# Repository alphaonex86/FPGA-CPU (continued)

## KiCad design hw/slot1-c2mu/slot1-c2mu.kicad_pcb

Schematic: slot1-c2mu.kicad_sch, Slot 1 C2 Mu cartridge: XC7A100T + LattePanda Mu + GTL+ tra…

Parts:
C1: 100uF/25V; CP_Elec_6.3x5.4
C2, C3, C10, C14, C18: 10uF/25V; C_1210_3225Metric
C4: 4.7uF/25V; C_0805_2012Metric
C5, C6: 22uF/10V; C_1206_3216Metric
C7, C12, C16, C20, C93, C94, C95, C96, C97, C98, C99, C100, C101, C102, C103, C104, C105, C106, C107, C108, C109, C110, C111, C112, C113, C114, C115, C116, C117, C118, C119, C120, C121, C122, C123, C124, C133, C134, C135, C136, C137, C138, C139, C141, C142, C146, C147, C148, C149, C150, C151, C169, C170, C171: 100nF; C_0402_1005Metric
C8: 10nF; C_0402_1005Metric
C9: 27nF; C_0402_1005Metric
C11, C15, C19: 22uF/6.3V; C_0805_2012Metric
C13, C17, C21: 3.3nF; C_0402_1005Metric
C22, C23, C24, C25, C26, C27, C28, C29, C30, C31, C32, C33, C34, C35, C36, C37, C38, C41, C42, C43, C44, C45: 470nF; C_0402_P1.00
C39, C40, C46, C47, C48, C49, C50, C51, C52: 470nF; C_0402_1005Metric
C53, C54, C55, C56, C57, C58, C59, C60, C61, C62, C63: 100nF; C_0402_P1.00
C64, C65: 100uF/6.3V; C_1210_3225Metric
C66, C67, C68, C69, C70, C71, C74, C75, C76, C77, C78, C83, C84, C85, C86, C87, C88, C89, C90, C91, C92, C140, C143: 4.7uF; C_0603_1608Metric
C72, C73, C79, C80, C81, C82: 47uF/6.3V; C_1210_3225Metric
C125, C126, C129, C130: 1uF; C_0402_1005Metric
C127, C131: 2.2uF; C_0402_1005Metric
C128, C132: 1nF; C_0402_1005Metric
C144, C145: 22uF; C_0805_2012Metric
C152: 10pF; C_0402_1005Metric
C153, C154, C155, C156, C157, C158, C159, C160, C161, C162, C163, C164, C165, C166, C167, C168: 220nF; C_0402_1005Metric
C172: 10uF; C_0805_2012Metric
C173, C174: 27pF; C_0402_1005Metric
D1: green; LED_0603_1608Metric
D2: B5819WS; D_SOD-323
F1: 5A; Fuse_1812_4532Metric
F2: 1.1A; Fuse_1206_3216Metric
FB1: 600R@100MHz; L_0603_1608Metric
H1, H2: MountingHole_Pad; Standoff_SMT_M2_D5.56_H6.6
J1: Conn_02x07_Odd_Even; PinHeader_2x07_P2.00mm_Vertical
J3: Barrel_Jack; BarrelJack_CUI_PJ-063AH_Horizontal
J4: LattePanda_Mu_SODIMM260; LattePanda_Mu_LOTES_ADDR0110_9.2H
J5: Conn_01x04; JST_PH_B4B-PH-K_1x04_P2.00mm_Vertical
J6: USB 2.0 x2 header; PinHeader_2x05_P2.54mm_Vertical
J7: Conn_01x03; PinHeader_1x03_P2.54mm_Vertical
J8: CMOS cell; Molex_PicoBlade_53261-0271_1x02-1MP_P1.25mm_Horizontal
L1: 6.8uH FXL1040-6R8; L_Changjiang_FXL1040
L2, L3, L4: 2.2uH XFL4020-222; L_Coilcraft_XxL4020
PS1: TPS54620RHL; TI_RHL0014A
PS2, PS3, PS4: TPS62130RGT; VQFN-16-1EP_3x3mm_P0.5mm_EP1.68x1.68mm
Q1, Q2: 2N7002; SOT-23
R1: 1.33k; R_0402_1005Metric
R2, R5, R7, R8, R10, R11, R13, R48, R49: 100k; R_0402_1005Metric
R3: 52.3k; R_0402_1005Metric
R4, R25, R26, R27, R28, R29, R44, R45, R47, R56, R57: 10k; R_0402_1005Metric
R6: 24.9k; R_0402_1005Metric
R9: 124k; R_0402_1005Metric
R12: 316k; R_0402_1005Metric
R14: 1.13k 1%; R_0402_1005Metric
R15: 4.53k 1%; R_0402_1005Metric
R16: 2.49k 1%; R_0402_1005Metric
R17: 4.99k 1%; R_0402_1005Metric
R18: 1.00k; R_0402_1005Metric
R19: 2.00k; R_0402_1005Metric
R20, R41, R53: 1k; R_0402_1005Metric
R21, R22, R23, R24: 0R; R_0402_1005Metric
R30, R31, R32, R33, R34, R35, R36, R37: 22R; R_0402_1005Metric
R38, R39, R42, R46, R52: 4.7k; R_0402_1005Metric
R40, R54: 330R; R_0402_1005Metric
R43: 100R 1%; R_0402_1005Metric
R50: 100R; R_0402_1005Metric
R51: 21.5k; R_0402_1005Metric
R55: 12k 1%; R_0402_1005Metric
R58, R59, R60, R61: 33R; R_0402_1005Metric
RN1, RN2, RN3, RN4, RN5, RN6, RN7, RN8, RN9, RN10, RN11, RN12, RN13, RN14, RN15, RN16, RN17, RN18, RN19, RN20, RN21, RN22, RN23, RN24, RN25, RN26, RN27, RN28, RN29, RN30, RN31, RN32, RN33, RN34, RN35: 56R; R_Array_Convex_4x0402
SW1: PWR; SW_Push_1P1T_XKB_TS-1187A
U1: FPGA_Artix7_XC7A100T_FGG484
U2: Intel_SC242_CardEdge
U3, U4, U5, U6, U7, U8, U9: SN74GTL16612; TSSOP-56_6.1x14mm_P0.5mm
U10: CY2309; SOIC-16_3.9x9.9mm_P1.27mm
U11: W25Q128JVSIQ; SOIC-8_5.3x5.3mm_P1.27mm
U12: 50MHz; Oscillator_SMD_SeikoEpson_SG210-4Pin_2.5x2.0mm
U13, U14: TPS74801; VSON-10-1EP_3x3mm_P0.5mm_EP1.65x2.4mm
U15, U17: USBLC6-2SC6; SOT-23-6
U16: FT232HL-REEL; LQFP-48_7x7mm_P0.5mm
Y1: 12MHz; Crystal_SMD_3225-4Pin_3.2x2.5mm

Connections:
/AB_LE: U1.AA21, U3.2 (LEAB), U4.2 (LEAB), U5.2 (LEAB), U6.2 (LEAB), U7.2 (LEAB), U8.2 (LEAB), U9.2 (LEAB)
/ADDR_OEAB#: R25.1, U1.V2, U3.1 (OEAB#), U4.1 (OEAB#)
/ADDR_OEBA#: R26.1, U1.AB7, U3.27 (OEBA#), U4.27 (OEBA#)
/A[3]#: U1.AA6, U4.10 (A6)
/A[4]#: U1.Y2, U4.16 (A11)
/A[5]#: U1.AB10, U4.6 (A3)
/A[6]#: U1.W2, U4.14 (A9)
/A[7]#: U1.AB11, U4.3 (A1)
/A[8]#: U1.AA8, U4.8 (A4)
/A[9]#: U1.AB6, U4.13 (A8)
/A[10]#: U1.AA9, U4.5 (A2)
/A[11]#: U1.AB13, U3.23 (A16)
/A[12]#: U1.AA5, U4.12 (A7)
/A[13]#: U1.AA4, U4.15 (A10)
/A[14]#: U1.AB8, U4.9 (A5)
/A[15]#: U1.AA15, U3.16 (A11)
/A[16]#: U1.AA3, U4.17 (A12)
/A[17]#: U1.AB15, U3.20 (A14)
/A[18]#: U1.Y13, U3.19 (A13)
/A[19]#: U1.AA16, U3.13 (A8)
/A[20]#: U1.AB22, U3.3 (A1)
/A[21]#: U1.AB21, U3.5 (A2)
/A[22]#: U1.AB20, U3.8 (A4)
/A[23]#: U1.AA19, U3.6 (A3)
/A[24]#: U1.Y14, U3.15 (A10)
/A[25]#: U1.AA18, U3.9 (A5)
/A[26]#: U1.AB16, U3.17 (A12)
/A[27]#: U1.AB18, U3.12 (A7)
/A[28]#: U1.Y16, U3.10 (A6)
/A[29]#: U1.Y9, U3.24 (A17)
/A[30]#: U1.Y12, U3.21 (A15)
/A[31]#: U1.AB17, U3.14 (A9)
/BCLK: U1.W19, U2.A75 (BCLK), U10.1 (REF)
/CFG_DONE: R40.1, U1.G11
/CFG_INIT_B: R39.1, U1.U12
/CFG_PROGRAM_B: R38.1, U1.N12
/CLK_ADDR0: R30.2, U3.30 (CLKBA), U3.55 (CLKAB)
/CLK_ADDR1: R31.2, U4.30 (CLKBA), U4.55 (CLKAB)
/CLK_DATA0: R32.2, U5.30 (CLKBA), U5.55 (CLKAB)
/CLK_DATA1: R33.2, U6.30 (CLKBA), U6.55 (CLKAB)
/CLK_DATA2: R34.2, U7.30 (CLKBA), U7.55 (CLKAB)
/CLK_DATA3: R35.2, U8.30 (CLKBA), U8.55 (CLKAB)
/CLK_FB: C152.1, R37.2
/CLK_TX: R36.2, U9.30 (CLKBA), U9.55 (CLKAB)
/DATA_OEAB#: R27.1, U1.D22, U5.1 (OEAB#), U6.1 (OEAB#), U7.1 (OEAB#), U8.1 (OEAB#)
/DATA_OEBA#: R28.1, U1.D21, U5.27 (OEBA#), U6.27 (OEBA#), U7.27 (OEBA#), U8.27 (OEBA#)
/D[0]#: U1.U21, U8.15 (A10)
/D[1]#: U1.W16, U8.19 (A13)
/D[2]#: U1.W22, U8.12 (A7)
/D[3]#: U1.U20, U8.16 (A11)
/D[4]#: U1.Y19, U8.8 (A4)
/D[5]#: U1.W21, U8.13 (A8)
/D[6]#: U1.Y21, U8.6 (A3)
/D[7]#: U1.Y17, U8.10 (A6)
/D[8]#: U1.AA20, U8.3 (A1)
/D[9]#: U1.Y22, U8.5 (A2)
/D[10]#: U1.W17, U8.17 (A12)
/D[11]#: U1.V20, U8.21 (A15)
/D[12]#: U1.W20, U8.14 (A9)
/D[13]#: U1.F19, U7.16 (A11)
/D[14]#: U1.Y18, U8.9 (A5)
/D[15]#: U1.V22, U8.20 (A14)
/D[16]#: U1.E22, U7.10 (A6)
/D[17]#: U1.V19, U8.23 (A16)
/D[18]#: U1.R19, U7.6 (A3)
/D[19]#: U1.T21, U7.3 (A1)
/D[20]#: U1.E19, U7.13 (A8)
/D[21]#: U1.P20, U7.8 (A4)
/D[22]#: U1.P19, U7.9 (A5)
/D[23]#: U1.T20, U7.5 (A2)
/D[24]#: U1.E21, U7.12 (A7)
/D[25]#: U1.F21, U7.14 (A9)
/D[26]#: U1.G21, U7.19 (A13)
/D[27]#: U1.F20, U7.15 (A10)
/D[28]#: U1.D16, U6.13 (A8)
/D[29]#: U1.M1, U7.20 (A14)
/D[30]#: U1.G22, U7.17 (A12)
/D[31]#: U1.L1, U7.21 (A15)
/D[32]#: U1.C19, U6.10 (A6)
/D[33]#: U1.C20, U6.9 (A5)
/D[34]#: U1.D17, U6.8 (A4)
/D[35]#: U1.K1, U7.23 (A16)
/D[36]#: U1.B21, U6.14 (A9)
/D[37]#: U1.D20, U6.3 (A1)
/D[38]#: U1.C22, U6.5 (A2)
/D[39]#: U1.C18, U6.15 (A10)
/D[40]#: U1.B22, U6.12 (A7)
/D[41]#: U1.B18, U6.21 (A15)
/D[42]#: U1.A21, U6.20 (A14)
/D[43]#: U1.D19, U6.6 (A3)
/D[44]#: U1.B20, U6.17 (A12)
/D[45]#: U1.D15, U6.16 (A11)
/D[46]#: U1.G2, U5.19 (A13)
/D[47]#: U1.C17, U6.19 (A13)
/D[48]#: U1.G1, U5.20 (A14)
/D[49]#: U1.F1, U5.21 (A15)
/D[50]#: U1.A15, U5.10 (A6)
/D[51]#: U1.A20, U6.23 (A16)
/D[52]#: U1.E2, U5.23 (A16)
/D[53]#: U1.A13, U5.14 (A9)
/D[54]#: U1.J2, U5.15 (A10)
/D[55]#: U1.A18, U5.3 (A1)
/D[56]#: U1.B15, U5.8 (A4)
/D[57]#: U1.J1, U5.16 (A11)
/D[58]#: U1.C14, U5.9 (A5)
/D[59]#: U1.H2, U5.17 (A12)
/D[60]#: U1.A14, U5.12 (A7)
/D[61]#: U1.C15, U5.6 (A3)
/D[62]#: U1.B13, U5.13 (A8)
/D[63]#: U1.B16, U5.5 (A2)
/FAN_PWM: J5.4, R50.2
/FAN_TAC: D2.2 (A), J5.3, R51.1, R52.1
/FT_EEDATA: R57.1, U16.43 (EEDATA)
/FT_REF: R55.1, U16.5 (REF)
/FT_RESET#: R56.1, U16.34 (~RESET)
/FT_TCK: R58.1, U16.13 (ADBUS0)
/FT_TDI: R59.1, U16.14 (ADBUS1)
/FT_TDO: R61.2, U16.15 (ADBUS2)
/FT_TMS: R60.1, U16.16 (ADBUS3)
/FT_VCCA: C142.1, U16.37 (VCCA)
/FT_VCORE: C141.1, U16.38 (VCCCORE)
/FT_VPHY: C138.1, C139.1, C140.1, FB1.2, U16.3 (VPHY), U16.8 (VPLL)
/FT_XI: C173.1, U16.1 (XCSI), Y1.1
/FT_XO: C174.1, U16.2 (XCSO), Y1.3
/F_TCK: J1.6, R46.1, R58.2, U1.V12
/F_TDI: J1.10, R45.1, R59.2, U1.R13
/F_TDO: J1.8, R61.1, U1.U13
/F_TMS: J1.4, R44.1, R60.2, U1.T13
/GND: C1.2, C2.2, C3.2, C4.2, C5.2, C6.2, C8.2, C9.2, C10.2, C11.2, C12.2, C13.2, C14.2, C15.2, C16.2, C17.2, C18.2, C19.2, C20.2, C21.2, C22.2, C23.2, C24.2, C25.2, C26.2, C27.2, C28.2, C29.2, C30.2, C31.2, C32.2, C33.2, C34.2, C35.2, C36.2, C37.2, C38.2, C39.2, C40.2, C41.2, C42.2, C43.2, C44.2, C45.2, C46.2, C47.2, C48.2, C49.2, C50.2, C51.2, C52.2, C53.2, C54.2, C55.2, C56.2, C57.2, C58.2, C59.2, C60.2, C61.2, C62.2, C63.2, C64.2, C65.2, C66.2, C67.2, C68.2, C69.2, C70.2, C71.2, C72.2, C73.2, C74.2, C75.2, C76.2, C77.2, C78.2, C79.2, C80.2, C81.2, C82.2, C83.2, C84.2, C85.2, C86.2, C87.2, C88.2, C89.2, C90.2, C91.2, C92.2, C93.2, C94.2, C95.2, C96.2, C97.2, C98.2, C99.2, C100.2, C101.2, C102.2, C103.2, C104.2, C105.2, C106.2, C107.2, C108.2, C109.2, C110.2, C111.2, C112.2, C113.2, C114.2, C115.2, C116.2, C117.2, C118.2, C119.2, C120.2, C121.2, C122.2, C123.2, C124.2, C125.2, C126.2, C127.2, C128.2, C129.2, C130.2, C131.2, C132.2, C133.2, C134.2, C135.2, C136.2, C137.2, C138.2, C139.2, C140.2, C141.2, C142.2, C143.2, C144.2, C145.2, C146.2, C147.2, C148.2, C149.2, C150.2, C151.2, C152.2, C171.2, C172.2, C173.2, C174.2, D1.1 (K), H1.1, H2.1, J1.1, J1.3, J1.5, J1.7, J1.9, J1.11, J1.13, J3.2, J4.11 (GND), J4.14 (GND), J4.17 (GND), J4.20 (GND), J4.23 (GND), J4.26 (GND), J4.29 (GND), J4.32 (GND), J4.35 (GND), J4.38 (GND), J4.41 (GND), J4.44 (GND), J4.47 (GND), J4.50 (GND), J4.53 (GND), J4.56 (GND), J4.59 (GND), J4.62 (GND), J4.65 (GND), J4.68 (GND), J4.71 (GND), J4.74 (GND), J4.77 (GND), J4.80 (GND), J4.83 (GND), J4.86 (GND), J4.89 (GND), J4.92 (GND), J4.95 (GND), J4.98 (GND), J4.101 (GND), J4.107 (GND), J4.110 (GND), J4.113 (GND), J4.116 (GND), J4.135 (GND), J4.136 (GND), J4.151 (GND), J4.158 (GND), J4.167 (GND), J4.170 (GND), J4.181 (GND), J4.182 (GND), J4.188 (GND), J4.189 (GND), J4.194 (GND), J4.195 (GND), J4.200 (GND), J4.201 (GND), J4.206 (GND), J4.207 (GND), J4.212 (GND), J4.213 (GND), J4.218 (GND), J4.219 (GND), J4.224 (GND), J4.225 (GND), J4.230 (GND), J4.231 (GND), J4.236 (GND), J4.237 (GND), J4.242 (GND), J4.243 (GND), J4.248 (GND), J4.249 (GND), J5.1, J6.7, J6.8, J7.1, J8.2, PS1.2 (GND), PS1.3 (GND), PS1.15 (PAD), PS2.6 (AGND), PS2.7 (FSW), PS2.8 (DEF), PS2.15 (PGND), PS2.16 (PGND), PS2.17 (PAD), PS3.6 (AGND), PS3.7 (FSW), PS3.8 (DEF), PS3.15 (PGND), PS3.16 (PGND), PS3.17 (PAD), PS4.6 (AGND), PS4.7 (FSW), PS4.8 (DEF), PS4.15 (PGND), PS4.16 (PGND), PS4.17 (PAD), Q1.2 (S), Q2.2 (S), R2.2, R4.2, R7.2, R10.2, R13.2, R15.2, R17.2, R19.2, R21.2, R22.2, R23.2, R24.2, R46.2, R48.2, R49.2, R55.2, SW1.2, U1.A2, U1.A3, U1.A5, U1.A7, U1.A9, U1.A11, U1.A12, U1.A22, U1.AA2, U1.AA12, U1.AA22, U1.AB9, U1.AB19, U1.B3, U1.B12, U1.B19, U1.C3, U1.C6, U1.C10, U1.C12, U1.C16, U1.D3, U1.D4, U1.D8, U1.D12, U1.D13, U1.E4, U1.E5, U1.E7, U1.E9, U1.E11, U1.E12, U1.E20, U1.F5, U1.F11, U1.F17, U1.G5, U1.G6, U1.G7, U1.G8, U1.G9, U1.G10, U1.G12, U1.G14, U1.H1, U1.H7, U1.H9, U1.H11, U1.H21, U1.J8, U1.J10, U1.J12, U1.J18, U1.K5, U1.K7, U1.K9, U1.K11, U1.K15, U1.L2, U1.L8, U1.L9, U1.L10, U1.L22, U1.M7, U1.M9, U1.M10, U1.M11, U1.M19, U1.N6, U1.N8, U1.N9, U1.N10, U1.N16, U1.P3, U1.P7, U1.P9, U1.P11, U1.P13, U1.R8, U1.R10, U1.R12, U1.R20, U1.T7, U1.T9, U1.T11, U1.T17, U1.U4, U1.U9, U1.U10, U1.U14, U1.V1, U1.V11, U1.V21, U1.W8, U1.W18, U1.Y5, U1.Y15, U2.A2 (GND), U2.A6 (GND), U2.A10 (GND), U2.A14 (GND), U2.A18 (GND), U2.A22 (GND), U2.A26 (GND), U2.A30 (GND), U2.A34 (GND), U2.A38 (GND), U2.A42 (GND), U2.A46 (GND), U2.A50 (GND), U2.A54 (GND), U2.A58 (GND), U2.A62 (GND), U2.A66 (GND), U2.A70 (GND), U2.A74 (GND), U2.A78 (GND), U2.A82 (GND), U2.A86 (GND), U2.A90 (GND), U2.A94 (GND), U2.A98 (GND), U2.A102 (GND), U2.A106 (GND), U2.A110 (GND), U2.A114 (GND), U2.A118 (GND), U2.B21 (100/66#), U2.B101 (SLOTOCC#), U3.4 (GND), U3.11 (GND), U3.18 (GND), U3.25 (GND), U3.29 (CEBA#), U3.32 (GND), U3.39 (GND), U3.46 (GND), U3.53 (GND), U3.56 (CEAB#), U4.4 (GND), U4.11 (GND), U4.18 (GND), U4.25 (GND), U4.29 (CEBA#), U4.32 (GND), U4.39 (GND), U4.46 (GND), U4.53 (GND), U4.56 (CEAB#), U5.4 (GND), U5.11 (GND), U5.18 (GND), U5.25 (GND), U5.28 (LEBA), U5.29 (CEBA#), U5.32 (GND), U5.39 (GND), U5.46 (GND), U5.53 (GND), U5.56 (CEAB#), U6.4 (GND), U6.11 (GND), U6.18 (GND), U6.25 (GND), U6.28 (LEBA), U6.29 (CEBA#), U6.32 (GND), U6.39 (GND), U6.46 (GND), U6.53 (GND), U6.56 (CEAB#), U7.4 (GND), U7.11 (GND), U7.18 (GND), U7.25 (GND), U7.28 (LEBA), U7.29 (CEBA#), U7.32 (GND), U7.39 (GND), U7.46 (GND), U7.53 (GND), U7.56 (CEAB#), U8.4 (GND), U8.11 (GND), U8.18 (GND), U8.25 (GND), U8.28 (LEBA), U8.29 (CEBA#), U8.32 (GND), U8.39 (GND), U8.46 (GND), U8.53 (GND), U8.56 (CEAB#), U9.4 (GND), U9.11 (GND), U9.18 (GND), U9.25 (GND), U9.28 (LEBA), U9.29 (CEBA#), U9.32 (GND), U9.39 (GND), U9.46 (GND), U9.53 (GND), U9.56 (CEAB#), U10.5 (GND), U10.12 (GND), U11.4 (GND), U12.2 (GND), U13.6 (GND), U13.11 (PAD), U14.6 (GND), U14.11 (PAD), U15.2 (GND), U16.4 (AGND), U16.9 (AGND), U16.10 (GND), U16.11 (GND), U16.22 (GND), U16.23 (GND), U16.35 (GND), U16.36 (GND), U16.41 (AGND), U16.42 (TEST), U16.47 (GND), U16.48 (GND), U17.2 (GND), Y1.2 (G), Y1.4 (G)
/LED: R54.2, U1.W1
/LED_A: D1.2 (A), R54.1
/MGT_RREF: R43.1, U1.F8
/MU_FAN_PWM: J4.2 (FAN2_CTL), R50.1
/MU_FAN_TAC: J4.4 (FAN2_TAC), R51.2
/MU_PSON: J4.5 (PSON), U1.R1
/MU_PWRBTN#: J4.1 (PWR_SW#), Q1.3 (D), SW1.1
/MU_PWR_ON: Q1.1 (G), R48.1, U1.P1
/MU_REFCLK_N: C170.2, J4.99 (REFCLK2_N)
/MU_REFCLK_P: C169.2, J4.97 (REFCLK2_P)
/MU_RST: Q2.1 (G), R49.1, U1.U1
/MU_RSTBTN#: J4.3 (RST_SW#), Q2.3 (D)
/MU_RX0_N: C154.2, J4.42 (HSIO8_RX_N)
/MU_RX0_P: C153.2, J4.40 (HSIO8_RX_P)
/MU_RX1_N: C156.2, J4.48 (HSIO9_RX_N)
/MU_RX1_P: C155.2, J4.46 (HSIO9_RX_P)
/MU_RX2_N: C158.2, J4.54 (HSIO10_RX_N)
/MU_RX2_P: C157.2, J4.52 (HSIO10_RX_P)
/MU_RX3_N: C160.2, J4.60 (HSIO11_RX_N)
/MU_RX3_P: C159.2, J4.58 (HSIO11_RX_P)
/MU_TX0_N: C162.2, J4.39 (HSIO8_TX_N)
/MU_TX0_P: C161.2, J4.37 (HSIO8_TX_P)
/MU_TX1_N: C164.2, J4.45 (HSIO9_TX_N)
/MU_TX1_P: C163.2, J4.43 (HSIO9_TX_P)
/MU_TX2_N: C166.2, J4.51 (HSIO10_TX_N)
/MU_TX2_P: C165.2, J4.49 (HSIO10_TX_P)
/MU_TX3_N: C168.2, J4.57 (HSIO11_TX_N)
/MU_TX3_P: C167.2, J4.55 (HSIO11_TX_P)
/MU_UART_RX: J4.137 (UART0_RXD), J7.3
/MU_UART_TX: J4.139 (UART0_TXD), J7.2
/MU_VBAT: J4.115 (VBAT), R53.2
/NC_D14: U1.D14
/NC_E3: U1.E3
/NC_E6: U1.E6
/NC_E13: U1.E13
/NC_E14: U1.E14
/NC_E16: U1.E16
/NC_E17: U1.E17
/NC_E18: U1.E18
/NC_F3: U1.F3
/NC_F4: U1.F4
/NC_F6: U1.F6
/NC_F13: U1.F13
/NC_F14: U1.F14
/NC_F15: U1.F15
/NC_F16: U1.F16
/NC_F18: U1.F18
/NC_G3: U1.G3
/NC_G4: U1.G4
/NC_G13: U1.G13
/NC_G15: U1.G15
/NC_G16: U1.G16
/NC_G17: U1.G17
/NC_G18: U1.G18
/NC_H3: U1.H3
/NC_H4: U1.H4
/NC_H5: U1.H5
/NC_H13: U1.H13
/NC_H14: U1.H14
/NC_H15: U1.H15
/NC_H17: U1.H17
/NC_H18: U1.H18
/NC_H19: U1.H19
/NC_J4: U1.J4
/NC_J5: U1.J5
/NC_J6: U1.J6
/NC_J14: U1.J14
/NC_J15: U1.J15
/NC_J16: U1.J16
/NC_J17: U1.J17
/NC_J19: U1.J19
/NC_K2: U1.K2
/NC_K3: U1.K3
/NC_K4: U1.K4
/NC_K6: U1.K6
/NC_K13: U1.K13
/NC_K14: U1.K14
/NC_K16: U1.K16
/NC_K17: U1.K17
/NC_K18: U1.K18
/NC_K19: U1.K19
/NC_L3: U1.L3
/NC_L4: U1.L4
/NC_L5: U1.L5
/NC_L6: U1.L6
/NC_L13: U1.L13
/NC_L14: U1.L14
/NC_L15: U1.L15
/NC_L16: U1.L16
/NC_L18: U1.L18
/NC_L19: U1.L19
/NC_M2: U1.M2
/NC_M3: U1.M3
/NC_M5: U1.M5
/NC_M6: U1.M6
/NC_M13: U1.M13
/NC_M15: U1.M15
/NC_M16: U1.M16
/NC_M17: U1.M17
/NC_M18: U1.M18
/NC_N2: U1.N2
/NC_N3: U1.N3
/NC_N4: U1.N4
/NC_N5: U1.N5
/NC_N13: U1.N13
/NC_N14: U1.N14
/NC_N15: U1.N15
/NC_N17: U1.N17
/NC_N18: U1.N18
/NC_P2: U1.P2
/NC_P4: U1.P4
/NC_P5: U1.P5
/NC_P6: U1.P6
/NC_P14: U1.P14
/NC_P15: U1.P15
/NC_P16: U1.P16
/NC_P17: U1.P17
/NC_PS1_10: PS1.10 (EN)
/NC_PS4_4: PS4.4 (PG)
/NC_R2: U1.R2
/NC_R3: U1.R3
/NC_R4: U1.R4
/NC_R6: U1.R6
/NC_R14: U1.R14
/NC_R16: U1.R16
/NC_R17: U1.R17
/NC_R18: U1.R18
/NC_RN35_2: RN35.2 (R2.1)
/NC_RN35_3: RN35.3 (R3.1)
/NC_RN35_4: RN35.4 (R4.1)
/NC_T3: U1.T3
/NC_T4: U1.T4
/NC_T5: U1.T5
/NC_T6: U1.T6
/NC_T14: U1.T14
/NC_T15: U1.T15
/NC_T16: U1.T16
/NC_T18: U1.T18
/NC_U2: U1.U2
/NC_U2_A4: U2.A4 (IERR#)
/NC_U2_A7: U2.A7 (FERR#)
/NC_U2_A9: U2.A9 (TDI)
/NC_U2_A11: U2.A11 (TDO)
/NC_U2_A13: U2.A13 (TESTHI)
/NC_U2_A16: U2.A16 (Reserved)
/NC_U2_A19: U2.A19 (PICD0)
/NC_U2_A20: U2.A20 (PREQ#)
/NC_U2_A47: U2.A47 (Reserved)
/NC_U2_A88: U2.A88 (Reserved)
/NC_U2_A113: U2.A113 (Reserved)
/NC_U2_A116: U2.A116 (Reserved)
/NC_U2_B1: U2.B1 (EMI)
/NC_U2_B7: U2.B7 (TCK)
/NC_U2_B10: U2.B10 (TMS)
/NC_U2_B11: U2.B11 (TRST#)
/NC_U2_B12: U2.B12 (Reserved)
/NC_U2_B13: U2.B13 (VCC_CORE)
/NC_U2_B14: U2.B14 (THERMDP)
/NC_U2_B15: U2.B15 (THERMDN)
/NC_U2_B17: U2.B17 (VCC_CORE)
/NC_U2_B18: U2.B18 (PICCLK)
/NC_U2_B20: U2.B20 (Reserved)
/NC_U2_B22: U2.B22 (PICD1)
/NC_U2_B25: U2.B25 (VCC_CORE)
/NC_U2_B29: U2.B29 (VCC_CORE)
/NC_U2_B33: U2.B33 (VCC_CORE)
/NC_U2_B37: U2.B37 (VCC_CORE)
/NC_U2_B41: U2.B41 (EMI)
/NC_U2_B45: U2.B45 (VCC_CORE)
/NC_U2_B49: U2.B49 (VCC_CORE)
/NC_U2_B53: U2.B53 (VCC_CORE)
/NC_U2_B57: U2.B57 (VCC_CORE)
/NC_U2_B61: U2.B61 (EMI)
/NC_U2_B65: U2.B65 (VCC_CORE)
/NC_U2_B69: U2.B69 (VCC_CORE)
/NC_U2_B73: U2.B73 (VCC_CORE)
/NC_U2_B76: U2.B76 (Reserved)
/NC_U2_B77: U2.B77 (VCC_CORE)
/NC_U2_B81: U2.B81 (EMI)
/NC_U2_B85: U2.B85 (VCC_CORE)
/NC_U2_B89: U2.B89 (VCC_CORE)
/NC_U2_B93: U2.B93 (VCC_CORE)
/NC_U2_B97: U2.B97 (VCC_CORE)
/NC_U2_B100: U2.B100 (EMI)
/NC_U2_B105: U2.B105 (VCC_CORE)
/NC_U2_B109: U2.B109 (VCC5)
/NC_U2_B112: U2.B112 (Reserved)
/NC_U2_B113: U2.B113 (VCC_L2)
/NC_U2_B117: U2.B117 (VCC_L2)
/NC_U2_B120: U2.B120 (VID0)
/NC_U2_B121: U2.B121 (VCC_L2)
/NC_U3: U1.U3
/NC_U5: U1.U5
/NC_U6: U1.U6
/NC_U7: U1.U7
/NC_U15: U1.U15
/NC_U16: U1.U16
/NC_U17: U1.U17
/NC_U18: U1.U18
/NC_V3: U1.V3
/NC_V4: U1.V4
/NC_V5: U1.V5
/NC_V7: U1.V7
/NC_V8: U1.V8
/NC_V9: U1.V9
/NC_V10: U1.V10
/NC_V13: U1.V13
/NC_V14: U1.V14
/NC_V15: U1.V15
/NC_V17: U1.V17
/NC_V18: U1.V18
/NC_W4: U1.W4
/NC_W5: U1.W5
/NC_W6: U1.W6
/NC_W7: U1.W7
/NC_W9: U1.W9
/NC_W10: U1.W10
/NC_W12: U1.W12
/NC_W14: U1.W14
/NC_W15: U1.W15
/NC_Y3: U1.Y3
/NC_Y4: U1.Y4
/NC_Y6: U1.Y6
/NC_Y7: U1.Y7
/OSC50: U1.W11, U12.3 (OUT)
/PCIE_PERST#: J4.105 (PLT_RST#), R47.1, U1.T1
/PCIE_REFCLK_N: C169.1, U1.E10
/PCIE_REFCLK_P: C170.1, U1.F10
/PCIE_RX0_N: C161.1, U1.C9
/PCIE_RX0_P: C162.1, U1.D9
/PCIE_RX1_N: C163.1, U1.A10
/PCIE_RX1_P: C164.1, U1.B10
/PCIE_RX2_N: C165.1, U1.C11
/PCIE_RX2_P: C166.1, U1.D11
/PCIE_RX3_N: C167.1, U1.A8
/PCIE_RX3_P: C168.1, U1.B8
/PCIE_TX0_N: C154.1, U1.C7
/PCIE_TX0_P: C153.1, U1.D7
/PCIE_TX1_N: C156.1, U1.A6
/PCIE_TX1_P: C155.1, U1.B6
/PCIE_TX2_N: C158.1, U1.C5
/PCIE_TX2_P: C157.1, U1.D5
/PCIE_TX3_N: C159.1, U1.A4
/PCIE_TX3_P: C160.1, U1.B4
/PG_1V0: PS2.4 (PG), PS3.13 (EN), R8.1
/PG_1V8: PS3.4 (PG), PS4.13 (EN), R11.1
/PG_5V: PS1.14 (PWRGD), PS2.13 (EN), R5.1
/PS1_BOOT: C7.1, PS1.13 (BOOT)
/PS1_COMP: PS1.8 (COMP), R1.1
/PS1_CZ: C9.1, R1.2
/PS1_FB: PS1.7 (VSENSE), R3.2, R4.1
/PS1_RT: PS1.1 (RT/CLK), R2.1
/PS1_SS: C8.1, PS1.9 (SS/TR)
/PS1_SW: C7.2, L1.1, PS1.11 (PH), PS1.12 (PH)
/PS2_FB: PS2.5 (FB), R6.2, R7.1
/PS2_SS: C13.1, PS2.9 (SS/TR)
/PS2_SW: L2.1, PS2.1 (SW), PS2.2 (SW), PS2.3 (SW)
/PS3_FB: PS3.5 (FB), R9.2, R10.1
/PS3_SS: C17.1, PS3.9 (SS/TR)
/PS3_SW: L3.1, PS3.1 (SW), PS3.2 (SW), PS3.3 (SW)
/PS4_FB: PS4.5 (FB), R12.2, R13.1
/PS4_SS: C21.1, PS4.9 (SS/TR)
/PS4_SW: L4.1, PS4.1 (SW), PS4.2 (SW), PS4.3 (SW)
/PUDC_B: R41.1, U1.U22
/REQ[0]#: U1.Y1, U4.19 (A13)
/REQ[1]#: U1.AB3, U4.20 (A14)
/REQ[2]#: U1.AB2, U4.23 (A16)
/REQ[3]#: U1.AB1, U4.24 (A17)
/REQ[4]#: U1.AA1, U4.21 (A15)
/RTC_CELL: J8.1, R53.1
/SPI_CLK: U1.L12, U11.6 (CLK)
/SPI_CS#: R42.1, U1.T19, U11.1 (~CS)
/SPI_D0: U1.P22, U11.5 (DI/IO_{0})
/SPI_D1: U1.R22, U11.2 (DO/IO_{1})
/SPI_D2: U1.P21, U11.3 (~WP/IO_{2})
/SPI_D3: U1.R21, U11.7 (~HOLD/~RESET/IO_{3})
/S_A20M#: U1.C2, U2.A5 (A20M#)
/S_ADS#: RN34.1 (R1.1), U1.N19, U2.A115 (ADS#), U9.45 (B7)
/S_AERR#: RN35.1 (R1.1), U2.B118 (AERR#)
/S_AP[0]#: RN34.4 (R4.1), U2.A117 (AP[0]#)
/S_AP[1]#: RN34.3 (R3.1), U2.B116 (AP[1]#)
/S_A[3]#: RN28.3 (R3.1), U2.B98 (A[3]#), U4.47 (B6)
/S_A[4]#: RN29.2 (R2.1), U2.A100 (A[4]#), U4.41 (B11)
/S_A[5]#: RN28.2 (R2.1), U2.A97 (A[5]#), U4.51 (B3)
/S_A[6]#: RN29.1 (R1.1), U2.B99 (A[6]#), U4.43 (B9)
/S_A[7]#: RN28.1 (R1.1), U2.B96 (A[7]#), U4.54 (B1)
/S_A[8]#: RN27.3 (R3.1), U2.B95 (A[8]#), U4.49 (B4)
/S_A[9]#: RN28.4 (R4.1), U2.A99 (A[9]#), U4.44 (B8)
/S_A[10]#: RN27.4 (R4.1), U2.A96 (A[10]#), U4.52 (B2)
/S_A[11]#: RN26.3 (R3.1), U2.B92 (A[11]#), U3.34 (B16)
/S_A[12]#: RN27.1 (R1.1), U2.B94 (A[12]#), U4.45 (B7)
/S_A[13]#: RN26.4 (R4.1), U2.A93 (A[13]#), U4.42 (B10)
/S_A[14]#: RN27.2 (R2.1), U2.A95 (A[14]#), U4.48 (B5)
/S_A[15]#: RN25.3 (R3.1), U2.B90 (A[15]#), U3.41 (B11)
/S_A[16]#: RN26.2 (R2.1), U2.A92 (A[16]#), U4.40 (B12)
/S_A[17]#: RN26.1 (R1.1), U2.B91 (A[17]#), U3.37 (B14)
/S_A[18]#: RN25.4 (R4.1), U2.A91 (A[18]#), U3.38 (B13)
/S_A[19]#: RN25.2 (R2.1), U2.A89 (A[19]#), U3.44 (B8)
/S_A[20]#: RN24.2 (R2.1), U2.B86 (A[20]#), U3.54 (B1)
/S_A[21]#: RN24.4 (R4.1), U2.B87 (A[21]#), U3.52 (B2)
/S_A[22]#: RN24.1 (R1.1), U2.A85 (A[22]#), U3.49 (B4)
/S_A[23]#: RN24.3 (R3.1), U2.A87 (A[23]#), U3.51 (B3)
/S_A[24]#: RN23.2 (R2.1), U2.B83 (A[24]#), U3.42 (B10)
/S_A[25]#: RN25.1 (R1.1), U2.B88 (A[25]#), U3.48 (B5)
/S_A[26]#: RN22.4 (R4.1), U2.B82 (A[26]#), U3.40 (B12)
/S_A[27]#: RN23.3 (R3.1), U2.A84 (A[27]#), U3.45 (B7)
/S_A[28]#: RN23.4 (R4.1), U2.B84 (A[28]#), U3.47 (B6)
/S_A[29]#: RN22.2 (R2.1), U2.B80 (A[29]#), U3.33 (B17)
/S_A[30]#: RN22.3 (R3.1), U2.A81 (A[30]#), U3.36 (B15)
/S_A[31]#: RN23.1 (R1.1), U2.A83 (A[31]#), U3.43 (B9)
/S_A[32]#: RN21.4 (R4.1), U2.B79 (A[32]#)
/S_A[33]#: RN21.3 (R3.1), U2.A79 (A[33]#)
/S_A[34]#: RN22.1 (R1.1), U2.A80 (A[34]#)
/S_A[35]#: RN21.2 (R2.1), U2.B78 (A[35]#)
/S_BERR#: RN21.1 (R1.1), U2.A77 (BERR#)
/S_BINIT#: RN2.1 (R1.1), U2.A24 (BINIT#)
/S_BNR#: RN29.3 (R3.1), U1.K22, U2.A101 (BNR#), U9.52 (B2)
/S_BPM[0]#: RN1.3 (R3.1), U2.A23 (BPM[0]#)
/S_BPM[1]#: RN2.2 (R2.1), U2.B24 (BPM[1]#)
/S_BPRI#: RN30.1 (R1.1), U1.J21, U2.A103 (BPRI#)
/S_BP[2]#: RN1.1 (R1.1), U2.B19 (BP[2]#)
/S_BP[3]#: RN1.2 (R2.1), U2.A21 (BP[3]#)
/S_BR0#: RN20.4 (R4.1), U1.J22, U2.A76 (BR0#), U9.54 (B1)
/S_BR1#: RN20.3 (R3.1), U2.B75 (BR1#)
/S_DBSY#: RN33.1 (R1.1), U1.L20, U2.A111 (DBSY#), U9.47 (B6)
/S_DEFER#: RN31.1 (R1.1), U1.K21, U2.A105 (DEFER#)
/S_DEP[0]#: RN2.3 (R3.1), U2.A25 (DEP[0]#)
/S_DEP[1]#: RN3.1 (R1.1), U2.A27 (DEP[1]#)
/S_DEP[2]#: RN2.4 (R4.1), U2.B26 (DEP[2]#)
/S_DEP[3]#: RN3.3 (R3.1), U2.A28 (DEP[3]#)
/S_DEP[4]#: RN3.2 (R2.1), U2.B27 (DEP[4]#)
/S_DEP[5]#: RN4.1 (R1.1), U2.A29 (DEP[5]#)
/S_DEP[6]#: RN4.3 (R3.1), U2.A31 (DEP[6]#)
/S_DEP[7]#: RN3.4 (R4.1), U2.B28 (DEP[7]#)
/S_DRDY#: RN31.4 (R4.1), U1.N22, U2.B107 (DRDY#), U9.51 (B3)
/S_D[0]#: RN20.1 (R1.1), U2.B72 (D[0]#), U8.42 (B10)
/S_D[1]#: RN20.2 (R2.1), U2.A73 (D[1]#), U8.38 (B13)
/S_D[2]#: RN19.3 (R3.1), U2.B71 (D[2]#), U8.45 (B7)
/S_D[3]#: RN19.4 (R4.1), U2.A72 (D[3]#), U8.41 (B11)
/S_D[4]#: RN19.1 (R1.1), U2.B70 (D[4]#), U8.49 (B4)
/S_D[5]#: RN19.2 (R2.1), U2.A71 (D[5]#), U8.44 (B8)
/S_D[6]#: RN18.3 (R3.1), U2.B68 (D[6]#), U8.51 (B3)
/S_D[7]#: RN18.1 (R1.1), U2.B67 (D[7]#), U8.47 (B6)
/S_D[8]#: RN18.4 (R4.1), U2.A69 (D[8]#), U8.54 (B1)
/S_D[9]#: RN18.2 (R2.1), U2.A68 (D[9]#), U8.52 (B2)
/S_D[10]#: RN17.2 (R2.1), U2.A65 (D[10]#), U8.40 (B12)
/S_D[11]#: RN16.4 (R4.1), U2.A64 (D[11]#), U8.36 (B15)
/S_D[12]#: RN17.3 (R3.1), U2.B66 (D[12]#), U8.43 (B9)
/S_D[13]#: RN16.2 (R2.1), U2.A63 (D[13]#), U7.41 (B11)
/S_D[14]#: RN17.4 (R4.1), U2.A67 (D[14]#), U8.48 (B5)
/S_D[15]#: RN17.1 (R1.1), U2.B64 (D[15]#), U8.37 (B14)
/S_D[16]#: RN15.4 (R4.1), U2.A61 (D[16]#), U7.47 (B6)
/S_D[17]#: RN16.3 (R3.1), U2.B63 (D[17]#), U8.34 (B16)
/S_D[18]#: RN15.3 (R3.1), U2.B60 (D[18]#), U7.51 (B3)
/S_D[19]#: RN15.1 (R1.1), U2.B59 (D[19]#), U7.54 (B1)
/S_D[20]#: RN16.1 (R1.1), U2.B62 (D[20]#), U7.44 (B8)
/S_D[21]#: RN15.2 (R2.1), U2.A60 (D[21]#), U7.49 (B4)
/S_D[22]#: RN14.3 (R3.1), U2.B58 (D[22]#), U7.48 (B5)
/S_D[23]#: RN14.4 (R4.1), U2.A59 (D[23]#), U7.52 (B2)
/S_D[24]#: RN14.2 (R2.1), U2.A57 (D[24]#), U7.45 (B7)
/S_D[25]#: RN14.1 (R1.1), U2.B56 (D[25]#), U7.43 (B9)
/S_D[26]#: RN13.3 (R3.1), U2.B55 (D[26]#), U7.38 (B13)
/S_D[27]#: RN13.4 (R4.1), U2.A56 (D[27]#), U7.42 (B10)
/S_D[28]#: RN12.3 (R3.1), U2.B52 (D[28]#), U6.44 (B8)
/S_D[29]#: RN13.1 (R1.1), U2.B54 (D[29]#), U7.37 (B14)
/S_D[30]#: RN13.2 (R2.1), U2.A55 (D[30]#), U7.40 (B12)
/S_D[31]#: RN12.4 (R4.1), U2.A53 (D[31]#), U7.36 (B15)
/S_D[32]#: RN12.1 (R1.1), U2.B51 (D[32]#), U6.47 (B6)
/S_D[33]#: RN11.4 (R4.1), U2.A51 (D[33]#), U6.48 (B5)
/S_D[34]#: RN11.1 (R1.1), U2.B48 (D[34]#), U6.49 (B4)
/S_D[35]#: RN12.2 (R2.1), U2.A52 (D[35]#), U7.34 (B16)
/S_D[36]#: RN10.2 (R2.1), U2.B46 (D[36]#), U6.43 (B9)
/S_D[37]#: RN11.2 (R2.1), U2.A49 (D[37]#), U6.54 (B1)
/S_D[38]#: RN11.3 (R3.1), U2.B50 (D[38]#), U6.52 (B2)
/S_D[39]#: RN10.1 (R1.1), U2.A45 (D[39]#), U6.42 (B10)
/S_D[40]#: RN10.3 (R3.1), U2.B47 (D[40]#), U6.45 (B7)
/S_D[41]#: RN8.4 (R4.1), U2.B42 (D[41]#), U6.36 (B15)
/S_D[42]#: RN9.1 (R1.1), U2.A43 (D[42]#), U6.37 (B14)
/S_D[43]#: RN10.4 (R4.1), U2.A48 (D[43]#), U6.51 (B3)
/S_D[44]#: RN9.4 (R4.1), U2.B44 (D[44]#), U6.40 (B12)
/S_D[45]#: RN9.3 (R3.1), U2.A44 (D[45]#), U6.41 (B11)
/S_D[46]#: RN7.3 (R3.1), U2.A39 (D[46]#), U5.38 (B13)
/S_D[47]#: RN9.2 (R2.1), U2.B43 (D[47]#), U6.38 (B13)
/S_D[48]#: RN7.4 (R4.1), U2.B39 (D[48]#), U5.37 (B14)
/S_D[49]#: RN8.1 (R1.1), U2.A40 (D[49]#), U5.36 (B15)
/S_D[50]#: RN6.2 (R2.1), U2.B35 (D[50]#), U5.47 (B6)
/S_D[51]#: RN8.3 (R3.1), U2.A41 (D[51]#), U6.34 (B16)
/S_D[52]#: RN8.2 (R2.1), U2.B40 (D[52]#), U5.34 (B16)
/S_D[53]#: RN6.3 (R3.1), U2.A36 (D[53]#), U5.43 (B9)
/S_D[54]#: RN6.4 (R4.1), U2.B36 (D[54]#), U5.42 (B10)
/S_D[55]#: RN5.3 (R3.1), U2.A33 (D[55]#), U5.54 (B1)
/S_D[56]#: RN5.4 (R4.1), U2.B34 (D[56]#), U5.49 (B4)
/S_D[57]#: RN7.1 (R1.1), U2.A37 (D[57]#), U5.41 (B11)
/S_D[58]#: RN4.4 (R4.1), U2.B31 (D[58]#), U5.48 (B5)
/S_D[59]#: RN7.2 (R2.1), U2.B38 (D[59]#), U5.40 (B12)
/S_D[60]#: RN6.1 (R1.1), U2.A35 (D[60]#), U5.45 (B7)
/S_D[61]#: RN5.1 (R1.1), U2.A32 (D[61]#), U5.51 (B3)
/S_D[62]#: RN4.2 (R2.1), U2.B30 (D[62]#), U5.44 (B8)
/S_D[63]#: RN5.2 (R2.1), U2.B32 (D[63]#), U5.52 (B2)
/S_FLUSH#: U1.A1, U2.B2 (FLUSH#)
/S_HIT#: RN32.4 (R4.1), U1.M21, U2.B110 (HIT#), U9.48 (B5)
/S_HITM#: RN32.3 (R3.1), U1.J20, U2.A109 (HITM#), U9.49 (B4)
/S_IGNNE#: U1.E1, U2.A8 (IGNNE#)
/S_INIT#: U1.B2, U2.B4 (INIT#)
/S_LINT[0]/INTR: U1.A19, U2.A17 (LINT[0]/INTR)
/S_LINT[1]/NMI: U1.B17, U2.B16 (LINT[1]/NMI)
/S_LOCK#: RN31.2 (R2.1), U1.H20, U2.B106 (LOCK#)
/S_PRDY#: RN1.4 (R4.1), U2.B23 (PRDY#)
/S_PWRGOOD: U1.C13, U2.A12 (PWRGOOD)
/S_REQ[0]#: RN29.4 (R4.1), U2.B102 (REQ[0]#), U4.38 (B13)
/S_REQ[1]#: RN30.2 (R2.1), U2.B103 (REQ[1]#), U4.37 (B14)
/S_REQ[2]#: RN31.3 (R3.1), U2.A107 (REQ[2]#), U4.34 (B16)
/S_REQ[3]#: RN32.1 (R1.1), U2.A108 (REQ[3]#), U4.33 (B17)
/S_REQ[4]#: RN30.4 (R4.1), U2.B104 (REQ[4]#), U4.36 (B15)
/S_RESET#: U1.H22, U2.B74 (RESET#)
/S_RP#: RN33.4 (R4.1), U2.B114 (RP#)
/S_RSP#: RN34.2 (R2.1), U2.B115 (RSP#)
/S_RS[0]#: RN32.2 (R2.1), U1.L21, U2.B108 (RS[0]#)
/S_RS[1]#: RN33.3 (R3.1), U1.N20, U2.A112 (RS[1]#)
/S_RS[2]#: RN33.2 (R2.1), U1.M20, U2.B111 (RS[2]#)
/S_SLP#: U1.D2, U2.B8 (SLP#)
/S_SMI#: U1.B1, U2.B3 (SMI#)
/S_STPCLK#: U1.D1, U2.B6 (STPCLK#)
/S_THERMTRIP#: U1.A16, U2.A15 (THERMTRIP#)
/S_TRDY#: RN30.3 (R3.1), U1.M22, U2.A104 (TRDY#)
/S_VID1: R21.1, U2.A120 (VID1)
/S_VID2: R22.1, U2.A119 (VID2)
/S_VID3: R23.1, U2.B119 (VID3)
/S_VID4: R24.1, U2.A121 (VID4)
/TX_ADS#: U1.Y8, U9.12 (A7)
/TX_BNR#: U1.AA13, U9.5 (A2)
/TX_BR0#: U1.AA14, U9.3 (A1)
/TX_DBSY#: U1.AA10, U9.10 (A6)
/TX_DRDY#: U1.Y11, U9.6 (A3)
/TX_HIT#: U1.AB12, U9.9 (A5)
/TX_HITM#: U1.AA11, U9.8 (A4)
/TX_OEAB#: R29.1, U1.AB5, U9.1 (OEAB#)
/U13_FB: R14.2, R15.1, U13.8 (FB)
/U13_SS: C128.1, U13.7 (SS)
/U14_FB: R16.2, R17.1, U14.8 (FB)
/U14_SS: C132.1, U14.7 (SS)
/USB1_N: J4.67 (USB2_P1_N), J6.3, U15.3 (I/O2), U15.4 (I/O2)
/USB1_P: J4.69 (USB2_P1_P), J6.5, U15.1 (I/O1), U15.6 (I/O1)
/USB2_N: J4.73 (USB2_P2_N), U16.6 (DM)
/USB2_P: J4.75 (USB2_P2_P), U16.7 (DP)
/USB3_N: J4.79 (USB2_P3_N), J6.4, U17.3 (I/O2), U17.4 (I/O2)
/USB3_P: J4.81 (USB2_P3_P), J6.6, U17.1 (I/O1), U17.6 (I/O1)
/USB_VBUS: C172.1, F2.2, J6.1, J6.2, U15.5 (VBUS), U17.5 (VBUS)
/V5: C5.1, C6.1, C10.1, C12.1, C14.1, C16.1, C18.1, C20.1, C95.1, C99.1, C103.1, C107.1, C111.1, C115.1, C119.1, C126.1, C130.1, C171.1, D2.1 (K), F2.1, J5.2, L1.2, PS2.10 (AVIN), PS2.11 (PVIN), PS2.12 (PVIN), PS3.10 (AVIN), PS3.11 (PVIN), PS3.12 (PVIN), PS4.10 (AVIN), PS4.11 (PVIN), PS4.12 (PVIN), R3.1, R5.2, R8.2, R11.2, R52.2, U3.50 (VCC5), U4.50 (VCC5), U5.50 (VCC5), U6.50 (VCC5), U7.50 (VCC5), U8.50 (VCC5), U9.50 (VCC5), U13.4 (BIAS), U14.4 (BIAS)
/V12: C1.1, C2.1, C3.1, C4.1, F1.2, J4.250 (VIN), J4.251 (VIN), J4.252 (VIN), J4.253 (VIN), J4.254 (VIN), J4.255 (VIN), J4.256 (VIN), J4.257 (VIN), J4.258 (VIN), J4.259 (VIN), J4.260 (VIN), PS1.4 (PVIN), PS1.5 (PVIN), PS1.6 (VIN)
/V12_IN: F1.1, J3.1
/VCC_1V0: C11.1, C22.1, C23.1, C24.1, C25.1, C26.1, C27.1, C28.1, C29.1, C30.1, C31.1, C64.1, C65.1, C66.1, C67.1, C68.1, C69.1, C70.1, C71.1, L2.2, PS2.14 (VOS), R6.1, U1.H8, U1.H10, U1.J7, U1.J9, U1.J11, U1.K8, U1.L7, U1.L11, U1.M8, U1.N7, U1.N11, U1.P8, U1.P10, U1.R7, U1.R9, U1.T8, U1.T10
/VCC_1V8: C15.1, C32.1, C33.1, C34.1, C35.1, C36.1, C37.1, C38.1, C39.1, C40.1, C72.1, C73.1, C74.1, C75.1, C76.1, C77.1, C78.1, C125.1, C129.1, L3.2, PS3.14 (VOS), R9.1, U1.G19, U1.H12, U1.H16, U1.J13, U1.K10, U1.K12, U1.K20, U1.L17, U1.M12, U1.N21, U1.P12, U1.R11, U13.1 (IN), U13.2 (IN), U13.5 (EN), U14.1 (IN), U14.2 (IN), U14.5 (EN)
/VCC_3V3: C19.1, C41.1, C42.1, C43.1, C44.1, C45.1, C46.1, C47.1, C48.1, C49.1, C50.1, C51.1, C52.1, C79.1, C80.1, C81.1, C82.1, C83.1, C84.1, C85.1, C86.1, C87.1, C88.1, C89.1, C90.1, C93.1, C94.1, C97.1, C98.1, C101.1, C102.1, C105.1, C106.1, C109.1, C110.1, C113.1, C114.1, C117.1, C118.1, C121.1, C122.1, C123.1, C124.1, C133.1, C134.1, C135.1, C136.1, C137.1, C143.1, FB1.1, J1.2, L4.2, PS4.14 (VOS), R12.1, R25.2, R26.2, R27.2, R28.2, R29.2, R38.2, R39.2, R40.2, R41.2, R42.2, R44.2, R45.2, R47.2, R56.2, R57.2, U1.A17, U1.AA7, U1.AA17, U1.AB4, U1.AB14, U1.B14, U1.C1, U1.C21, U1.D18, U1.E15, U1.F2, U1.F12, U1.F22, U1.H6, U1.J3, U1.M4, U1.M14, U1.N1, U1.P18, U1.R5, U1.R15, U1.T2, U1.T12, U1.T22, U1.U8, U1.U11, U1.U19, U1.V6, U1.V16, U1.W3, U1.W13, U1.Y10, U1.Y20, U3.7 (VCC33), U3.22 (VCC33), U3.28 (LEBA), U4.7 (VCC33), U4.22 (VCC33), U4.28 (LEBA), U5.7 (VCC33), U5.22 (VCC33), U6.7 (VCC33), U6.22 (VCC33), U7.7 (VCC33), U7.22 (VCC33), U8.7 (VCC33), U8.22 (VCC33), U9.7 (VCC33), U9.22 (VCC33), U9.27 (OEBA#), U10.4 (VDD), U10.8 (S2), U10.9 (S1), U10.13 (VDD), U11.8 (VCC), U12.1 (EN), U12.4 (Vdd), U16.12 (VCCIO), U16.24 (VCCIO), U16.39 (VCCD), U16.40 (VREGIN), U16.46 (VCCIO)
/VCC_MGT10: C53.1, C54.1, C55.1, C56.1, C57.1, C91.1, C127.1, R14.1, U1.D6, U1.D10, U1.E8, U1.F7, U1.F9, U13.9 (OUT), U13.10 (OUT)
/VCC_MGT12: C58.1, C59.1, C60.1, C61.1, C62.1, C63.1, C92.1, C131.1, R16.1, R43.2, U1.B5, U1.B7, U1.B9, U1.B11, U1.C4, U1.C8, U14.9 (OUT), U14.10 (OUT)
/VREF_GTL: C96.1, C100.1, C104.1, C108.1, C112.1, C116.1, C120.1, R18.2, R19.1, U3.35 (VREF), U4.35 (VREF), U5.35 (VREF), U6.35 (VREF), U7.35 (VREF), U8.35 (VREF), U9.35 (VREF)
/VTT15: C144.1, C145.1, C146.1, C147.1, C148.1, C149.1, C150.1, C151.1, R18.1, R20.1, RN1.5 (R4.2), RN1.6 (R3.2), RN1.7 (R2.2), RN1.8 (R1.2), RN2.5 (R4.2), RN2.6 (R3.2), RN2.7 (R2.2), RN2.8 (R1.2), RN3.5 (R4.2), RN3.6 (R3.2), RN3.7 (R2.2), RN3.8 (R1.2), RN4.5 (R4.2), RN4.6 (R3.2), RN4.7 (R2.2), RN4.8 (R1.2), RN5.5 (R4.2), RN5.6 (R3.2), RN5.7 (R2.2), RN5.8 (R1.2), RN6.5 (R4.2), RN6.6 (R3.2), RN6.7 (R2.2), RN6.8 (R1.2), RN7.5 (R4.2), RN7.6 (R3.2), RN7.7 (R2.2), RN7.8 (R1.2), RN8.5 (R4.2), RN8.6 (R3.2), RN8.7 (R2.2), RN8.8 (R1.2), RN9.5 (R4.2), RN9.6 (R3.2), RN9.7 (R2.2), RN9.8 (R1.2), RN10.5 (R4.2), RN10.6 (R3.2), RN10.7 (R2.2), RN10.8 (R1.2), RN11.5 (R4.2), RN11.6 (R3.2), RN11.7 (R2.2), RN11.8 (R1.2), RN12.5 (R4.2), RN12.6 (R3.2), RN12.7 (R2.2), RN12.8 (R1.2), RN13.5 (R4.2), RN13.6 (R3.2), RN13.7 (R2.2), RN13.8 (R1.2), RN14.5 (R4.2), RN14.6 (R3.2), RN14.7 (R2.2), RN14.8 (R1.2), RN15.5 (R4.2), RN15.6 (R3.2), RN15.7 (R2.2), RN15.8 (R1.2), RN16.5 (R4.2), RN16.6 (R3.2), RN16.7 (R2.2), RN16.8 (R1.2), RN17.5 (R4.2), RN17.6 (R3.2), RN17.7 (R2.2), RN17.8 (R1.2), RN18.5 (R4.2), RN18.6 (R3.2), RN18.7 (R2.2), RN18.8 (R1.2), RN19.5 (R4.2), RN19.6 (R3.2), RN19.7 (R2.2), RN19.8 (R1.2), RN20.5 (R4.2), RN20.6 (R3.2), RN20.7 (R2.2), RN20.8 (R1.2), RN21.5 (R4.2), RN21.6 (R3.2), RN21.7 (R2.2), RN21.8 (R1.2), RN22.5 (R4.2), RN22.6 (R3.2), RN22.7 (R2.2), RN22.8 (R1.2), RN23.5 (R4.2), RN23.6 (R3.2), RN23.7 (R2.2), RN23.8 (R1.2), RN24.5 (R4.2), RN24.6 (R3.2), RN24.7 (R2.2), RN24.8 (R1.2), RN25.5 (R4.2), RN25.6 (R3.2), RN25.7 (R2.2), RN25.8 (R1.2), RN26.5 (R4.2), RN26.6 (R3.2), RN26.7 (R2.2), RN26.8 (R1.2), RN27.5 (R4.2), RN27.6 (R3.2), RN27.7 (R2.2), RN27.8 (R1.2), RN28.5 (R4.2), RN28.6 (R3.2), RN28.7 (R2.2), RN28.8 (R1.2), RN29.5 (R4.2), RN29.6 (R3.2), RN29.7 (R2.2), RN29.8 (R1.2), RN30.5 (R4.2), RN30.6 (R3.2), RN30.7 (R2.2), RN30.8 (R1.2), RN31.5 (R4.2), RN31.6 (R3.2), RN31.7 (R2.2), RN31.8 (R1.2), RN32.5 (R4.2), RN32.6 (R3.2), RN32.7 (R2.2), RN32.8 (R1.2), RN33.5 (R4.2), RN33.6 (R3.2), RN33.7 (R2.2), RN33.8 (R1.2), RN34.5 (R4.2), RN34.6 (R3.2), RN34.7 (R2.2), RN34.8 (R1.2), RN35.5 (R4.2), RN35.6 (R3.2), RN35.7 (R2.2), RN35.8 (R1.2), U2.A1 (VCC_VTT), U2.A3 (VCC_VTT), U2.B5 (VCC_VTT), U2.B9 (VCC_VTT)
/VTT_SENSE: R20.2, U1.G20
/ZCLK_ADDR0: R30.1, U10.2 (CLKA1)
/ZCLK_ADDR1: R31.1, U10.3 (CLKA2)
/ZCLK_DATA0: R32.1, U10.14 (CLKA3)
/ZCLK_DATA1: R33.1, U10.15 (CLKA4)
/ZCLK_DATA2: R34.1, U10.6 (CLKB1)
/ZCLK_DATA3: R35.1, U10.7 (CLKB2)
/ZCLK_FB: R37.1, U10.16 (CLKOUT)
/ZCLK_TX: R36.1, U10.10 (CLKB3)

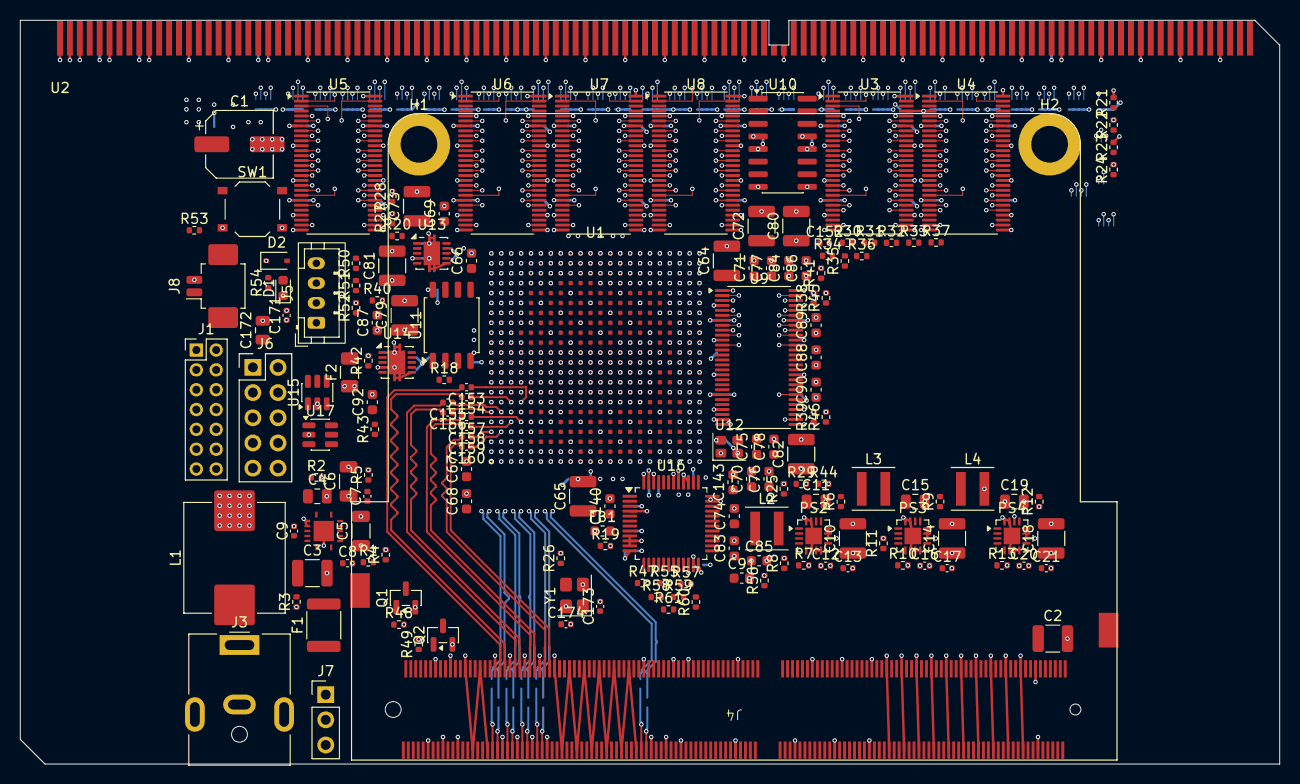
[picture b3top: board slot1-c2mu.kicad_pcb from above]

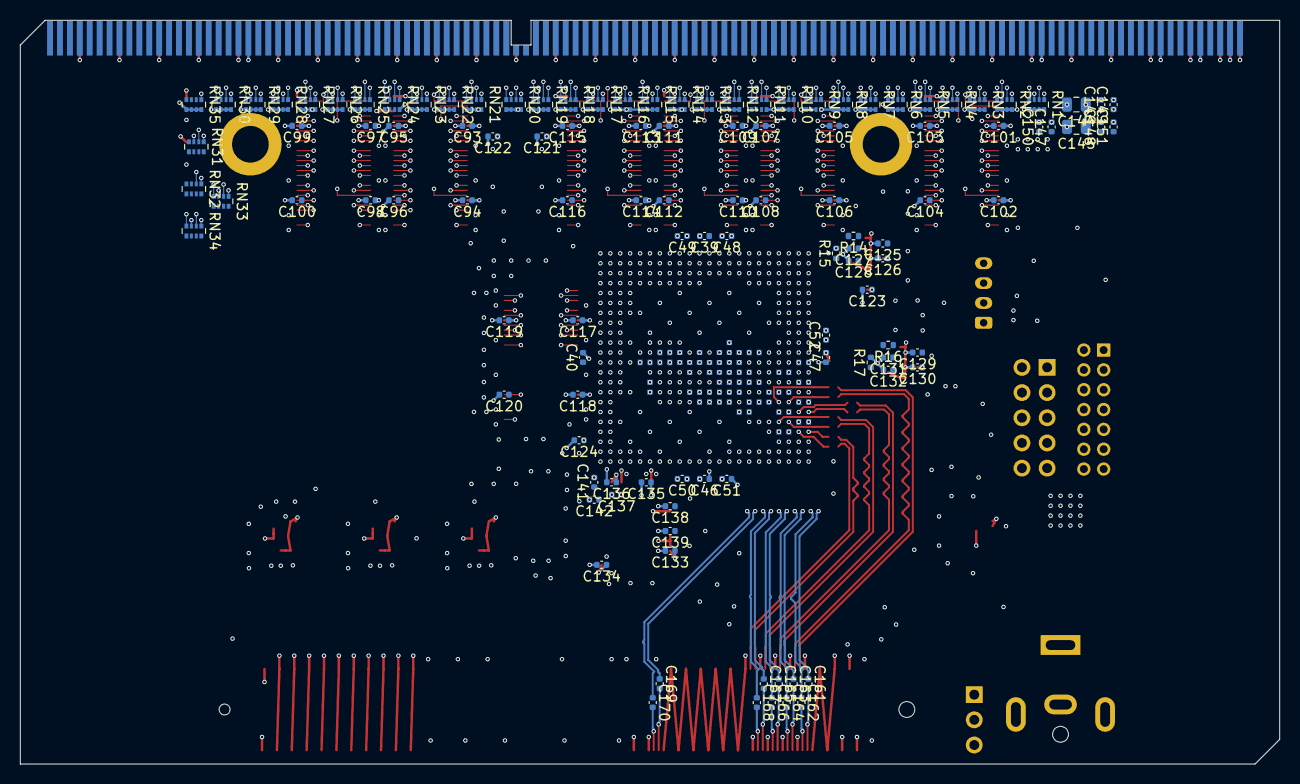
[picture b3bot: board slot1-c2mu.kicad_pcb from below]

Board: 8 copper layers, 127.0 x 75.0 mm, 313 parts (148 on the bottom side), 403 nets.
